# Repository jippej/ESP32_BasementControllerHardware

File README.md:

# JEEC Basement Controller Board
 A sensor and controller board based on WT32-ETH01

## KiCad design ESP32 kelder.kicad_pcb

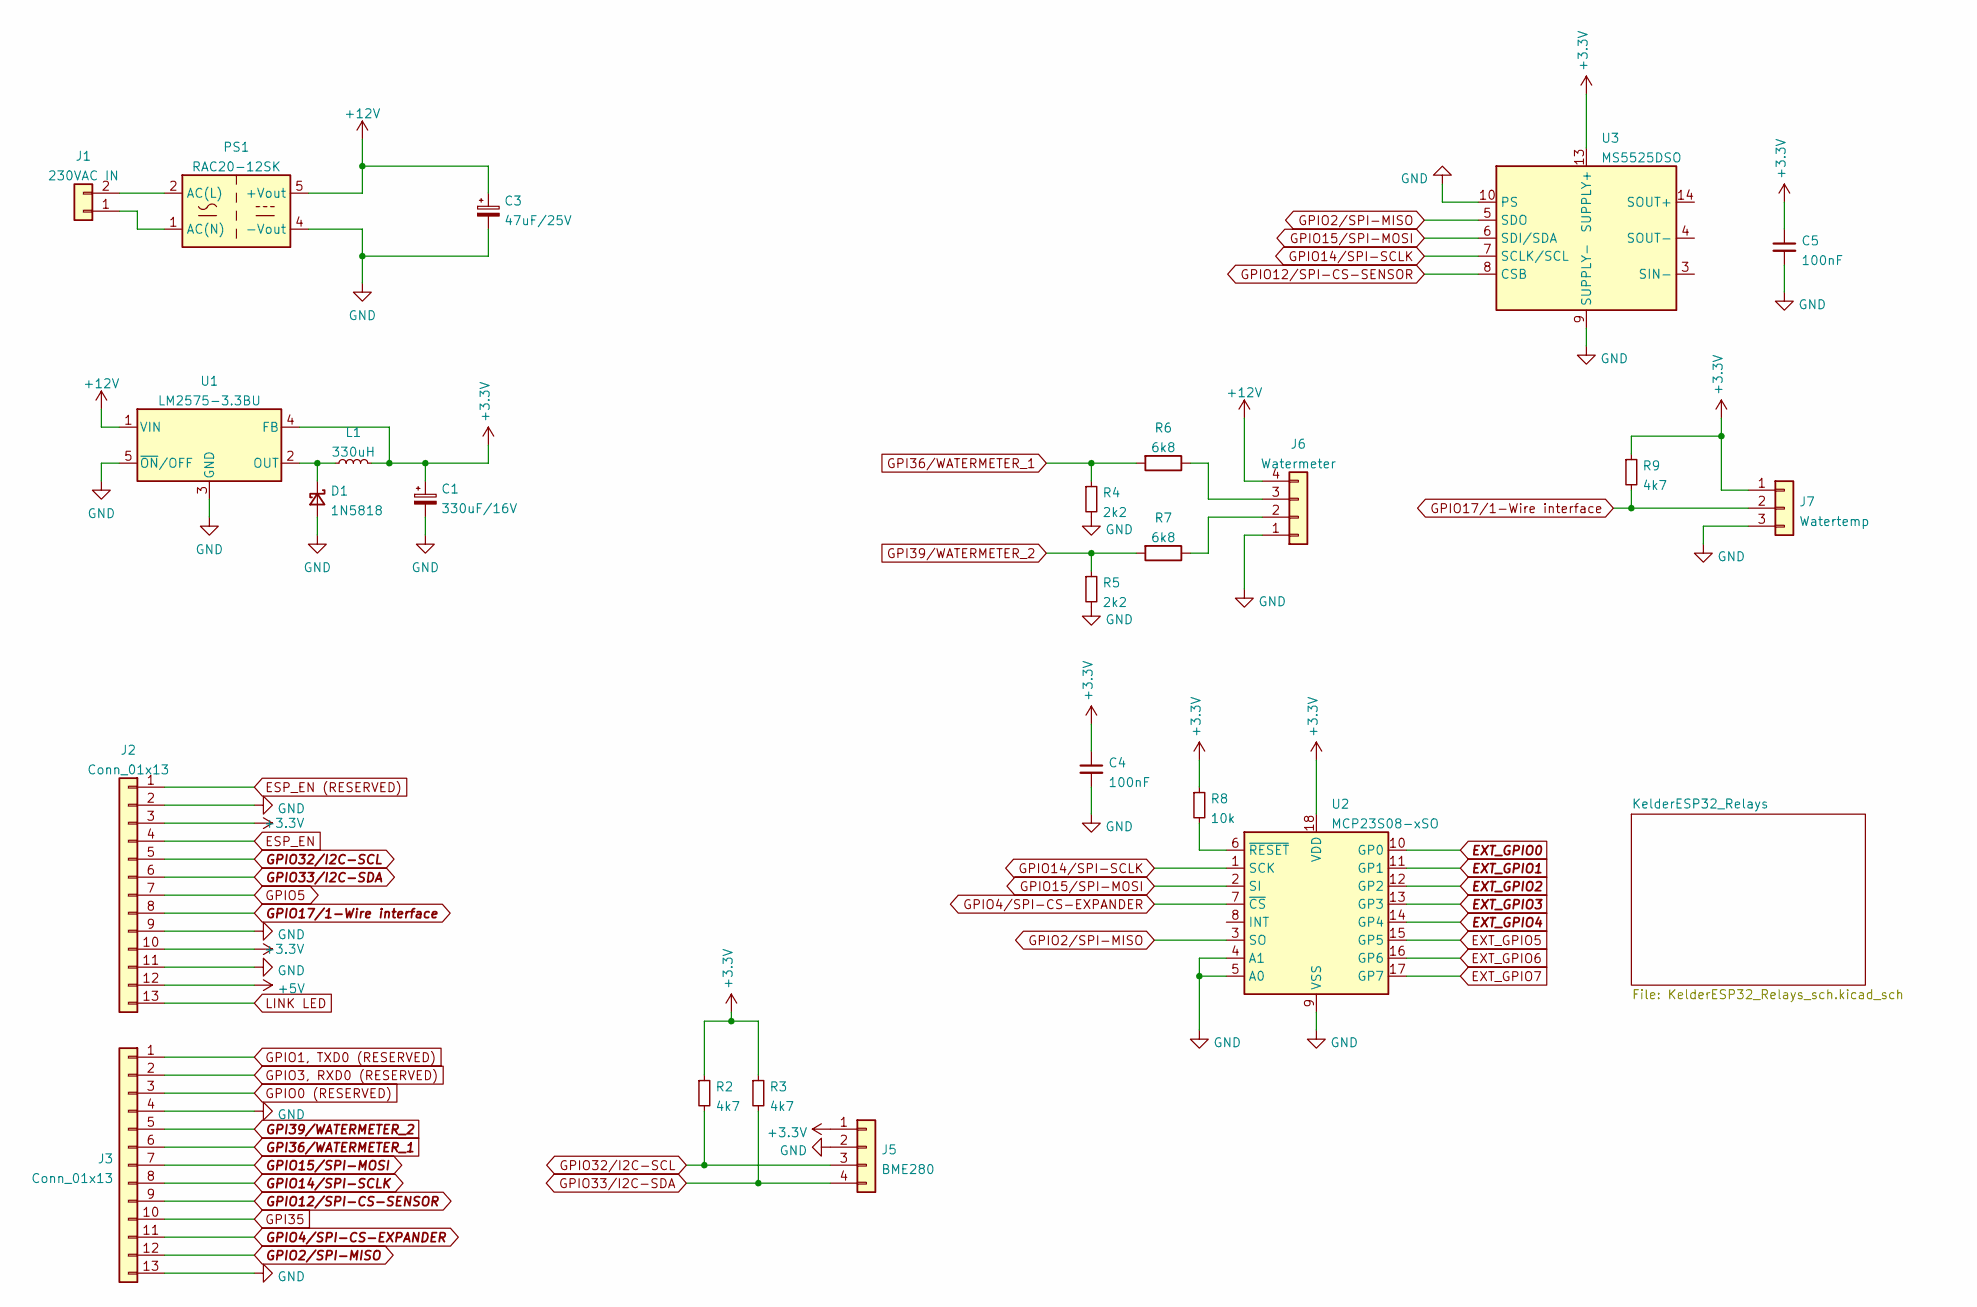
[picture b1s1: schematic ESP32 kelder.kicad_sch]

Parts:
C1: 330uF/16V; CP_Elec_8x10.5
C3: 47uF/25V; CP_Radial_D5.0mm_P2.00mm
C4, C5: 100nF; C_0805_2012Metric_Pad1.18x1.45mm_HandSolder
D1: 1N5818; D_DO-41_SOD81_P10.16mm_Horizontal
J1: 230VAC IN; TerminalBlock_Phoenix_MKDS-3-2-5.08_1x02_P5.08mm_Horizontal
J2, J3: Conn_01x13; PinSocket_1x13_P2.54mm_Vertical
J5: BME280; TerminalBlock_Phoenix_MKDS-1,5-4-5.08_1x04_P5.08mm_Horizont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
J6: Watermeter; TerminalBlock_Phoenix_MKDS-1,5-4-5.08_1x04_P5.08mm_Horizont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
J7: Watertemp; TerminalBlock_Phoenix_MKDS-1,5-3-5.08_1x03_P5.08mm_Horizont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
L1: 330uH; L_Bourns-SRN1060
PS1: RAC20-12SK; Converter_ACDC_Recom_RAC20-xxSK_THT
R2, R3, R9: 4k7; R_0805_2012Metric_Pad1.20x1.40mm_HandSolder
R4, R5: 2k2; R_0805_2012Metric_Pad1.20x1.40mm_HandSolder
R6, R7: 6k8; R_0805_2012Metric_Pad1.20x1.40mm_HandSolder
R8: 10k; R_0805_2012Metric_Pad1.20x1.40mm_HandSolder
U1: LM2575-3.3BU; TO-263-5_TabPin3
U2: MCP23S08-xSO; SOIC-18W_7.5x11.6mm_P1.27mm
U3: MS5525DSO; SOIC-14W_7.5x9mm_P1.27mm

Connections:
+3V3: C1.1, C4.1, C5.1, J2.3, J2.10, J5.1, J7.1, L1.2, R2.1, R3.1, R8.1, R9.1, U1.4 (FB), U2.18 (VDD), U3.11 (SUPPLY+), U3.13 (SUPPLY+)
+5V: J2.12
+12V: C3.1, J6.4, PS1.5 (+Vout), U1.1 (VIN); also elsewhere on the board
ESP_EN: J2.4
ESP_EN (RESERVED): J2.1
EXT_GPIO0: U2.10 (GP0); also elsewhere on the board
EXT_GPIO1: U2.11 (GP1); also elsewhere on the board
EXT_GPIO2: U2.12 (GP2); also elsewhere on the board
EXT_GPIO3: U2.13 (GP3); also elsewhere on the board
EXT_GPIO4: U2.14 (GP4); also elsewhere on the board
EXT_GPIO5: U2.15 (GP5)
EXT_GPIO6: U2.16 (GP6)
EXT_GPIO7: U2.17 (GP7)
GND: C1.2, C3.2, C4.2, C5.2, D1.2 (A), J2.2, J2.9, J2.11, J3.4, J3.13, J5.2, J6.1, J7.3, PS1.4 (-Vout), R4.2, R5.2, U1.3 (GND), U1.5 (~ON/OFF), U2.4 (A1), U2.5 (A0), U2.9 (VSS), U3.9 (SUPPLY-), U3.10 (PS); also elsewhere on the board
GPI35: J3.10
GPI36/WATERMETER_1: J3.6, R4.1, R6.2
GPI39/WATERMETER_2: J3.5, R5.1, R7.2
GPIO0 (RESERVED): J3.3
GPIO1, TXD0 (RESERVED): J3.1
GPIO2/SPI-MISO: J3.12, U2.3 (SO), U3.5 (SDO)
GPIO3, RXD0 (RESERVED): J3.2
GPIO4/SPI-CS-EXPANDER: J3.11, U2.7 (~CS)
GPIO5: J2.7
GPIO12/SPI-CS-SENSOR: J3.9, U3.8 (CSB)
GPIO14/SPI-SCLK: J3.8, U2.1 (SCK), U3.7 (SCLK/SCL)
GPIO15/SPI-MOSI: J3.7, U2.2 (SI), U3.6 (SDI/SDA)
GPIO17/1-Wire interface: J2.8, J7.2, R9.2
GPIO32/I2C-SCL: J2.5, J5.3, R2.2
GPIO33/I2C-SDA: J2.6, J5.4, R3.2
LINK LED: J2.13
unnamed: D1.1 (K), L1.1, U1.2 (OUT)
unnamed: J1.1, PS1.1 (AC(N))
unnamed: J1.2, PS1.2 (AC(L))
unnamed: J6.2, R7.1
unnamed: J6.3, R6.1
unnamed: R8.2, U2.6 (~RESET)
unnamed: U3.1 (SIN-), U3.3 (SIN-)
unnamed: U3.2 (SOUT-), U3.4 (SOUT-)
unnamed: U3.12 (SOUT+), U3.14 (SOUT+)

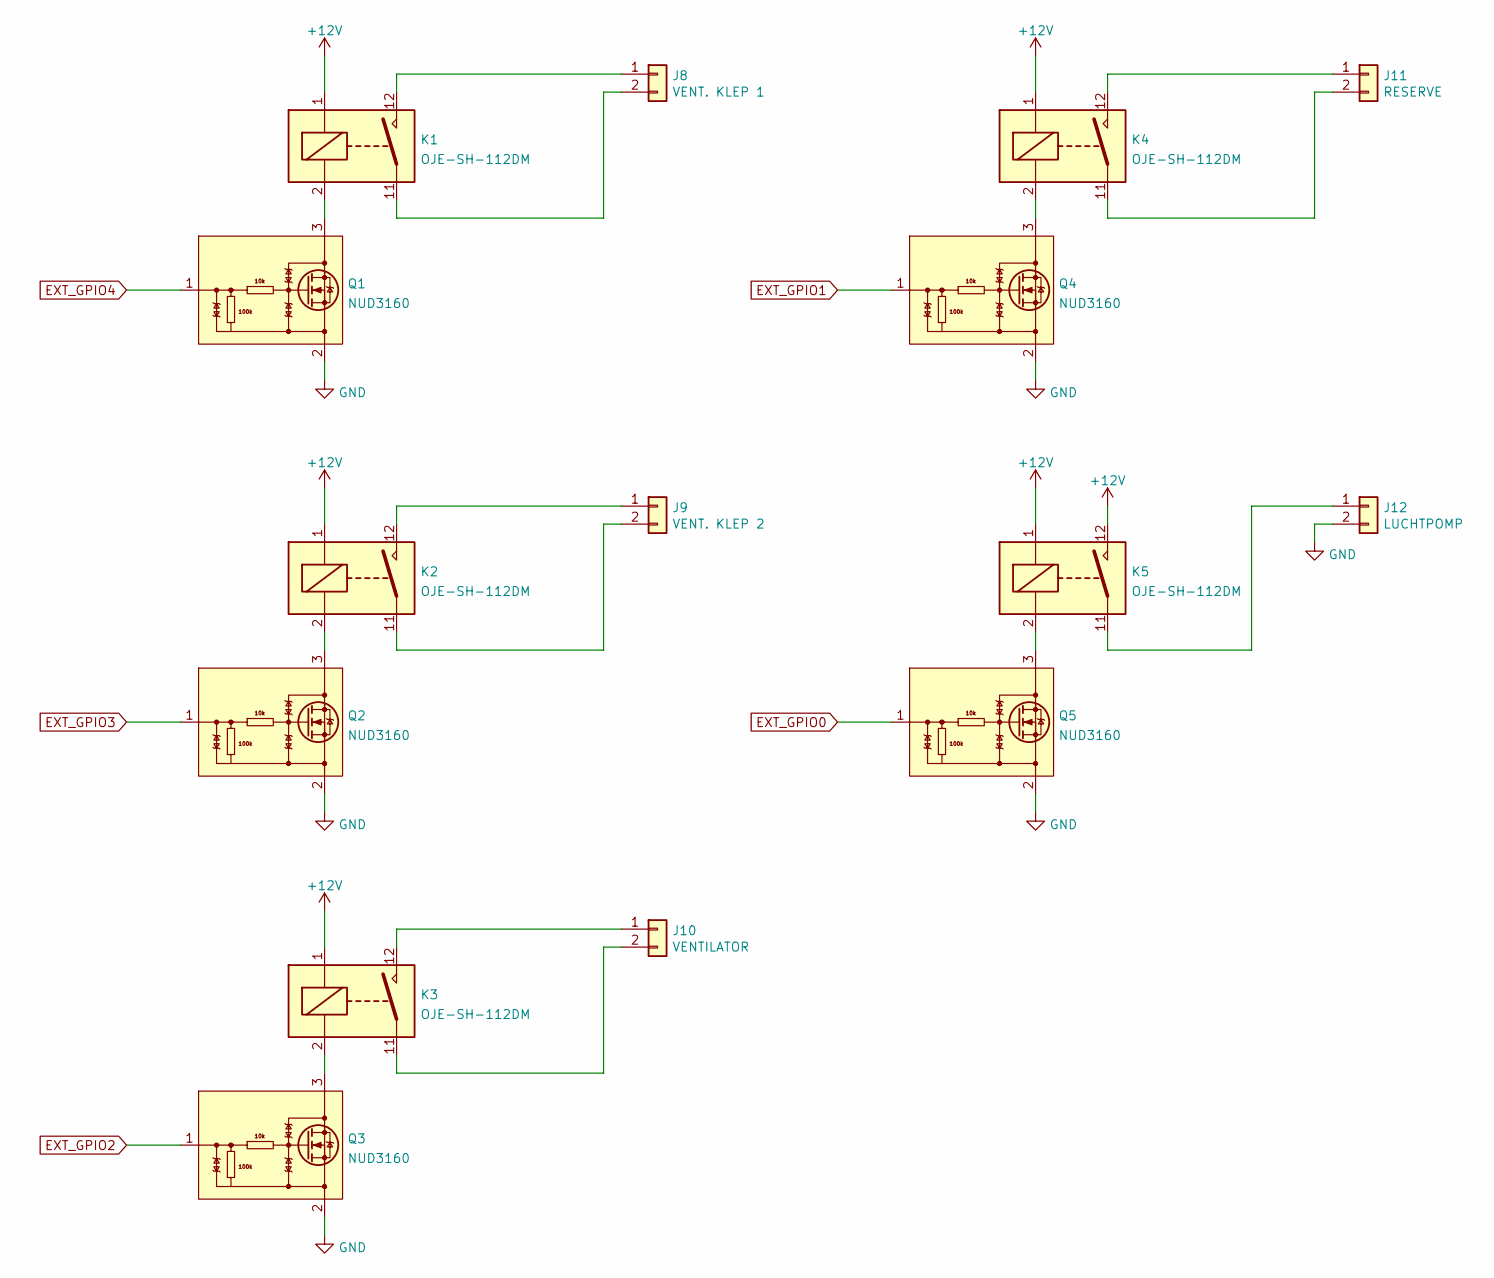
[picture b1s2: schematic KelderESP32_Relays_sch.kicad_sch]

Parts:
J8: VENT. KLEP 1; TerminalBlock_Phoenix_MKDS-3-2-5.08_1x02_P5.08mm_Horizontal
J9: VENT. KLEP 2; TerminalBlock_Phoenix_MKDS-3-2-5.08_1x02_P5.08mm_Horizontal
J10: VENTILATOR; TerminalBlock_Phoenix_MKDS-3-2-5.08_1x02_P5.08mm_Horizontal
J11: RESERVE; TerminalBlock_Phoenix_MKDS-3-2-5.08_1x02_P5.08mm_Horizontal
J12: LUCHTPOMP; TerminalBlock_Phoenix_MKDS-3-2-5.08_1x02_P5.08mm_Horizontal
K1, K2, K3, K4, K5: OJE-SH-112DM
Q1, Q2, Q3, Q4, Q5: NUD3160; SOT-23

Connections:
+12V: K1.1, K2.1, K3.1, K4.1, K5.1, K5.12; also elsewhere on the board
EXT_GPIO0: Q5.1 (G); also elsewhere on the board
EXT_GPIO1: Q4.1 (G); also elsewhere on the board
EXT_GPIO2: Q3.1 (G); also elsewhere on the board
EXT_GPIO3: Q2.1 (G); also elsewhere on the board
EXT_GPIO4: Q1.1 (G); also elsewhere on the board
GND: J12.2, Q1.2 (S), Q2.2 (S), Q3.2 (S), Q4.2 (S), Q5.2 (S); also elsewhere on the board
unnamed: J8.1, K1.12
unnamed: J8.2, K1.11
unnamed: J9.1, K2.12
unnamed: J9.2, K2.11
unnamed: J10.1, K3.12
unnamed: J10.2, K3.11
unnamed: J11.1, K4.12
unnamed: J11.2, K4.11
unnamed: J12.1, K5.11
unnamed: K1.2, Q1.3 (D)
unnamed: K2.2, Q2.3 (D)
unnamed: K3.2, Q3.3 (D)
unnamed: K4.2, Q4.3 (D)
unnamed: K5.2, Q5.3 (D)

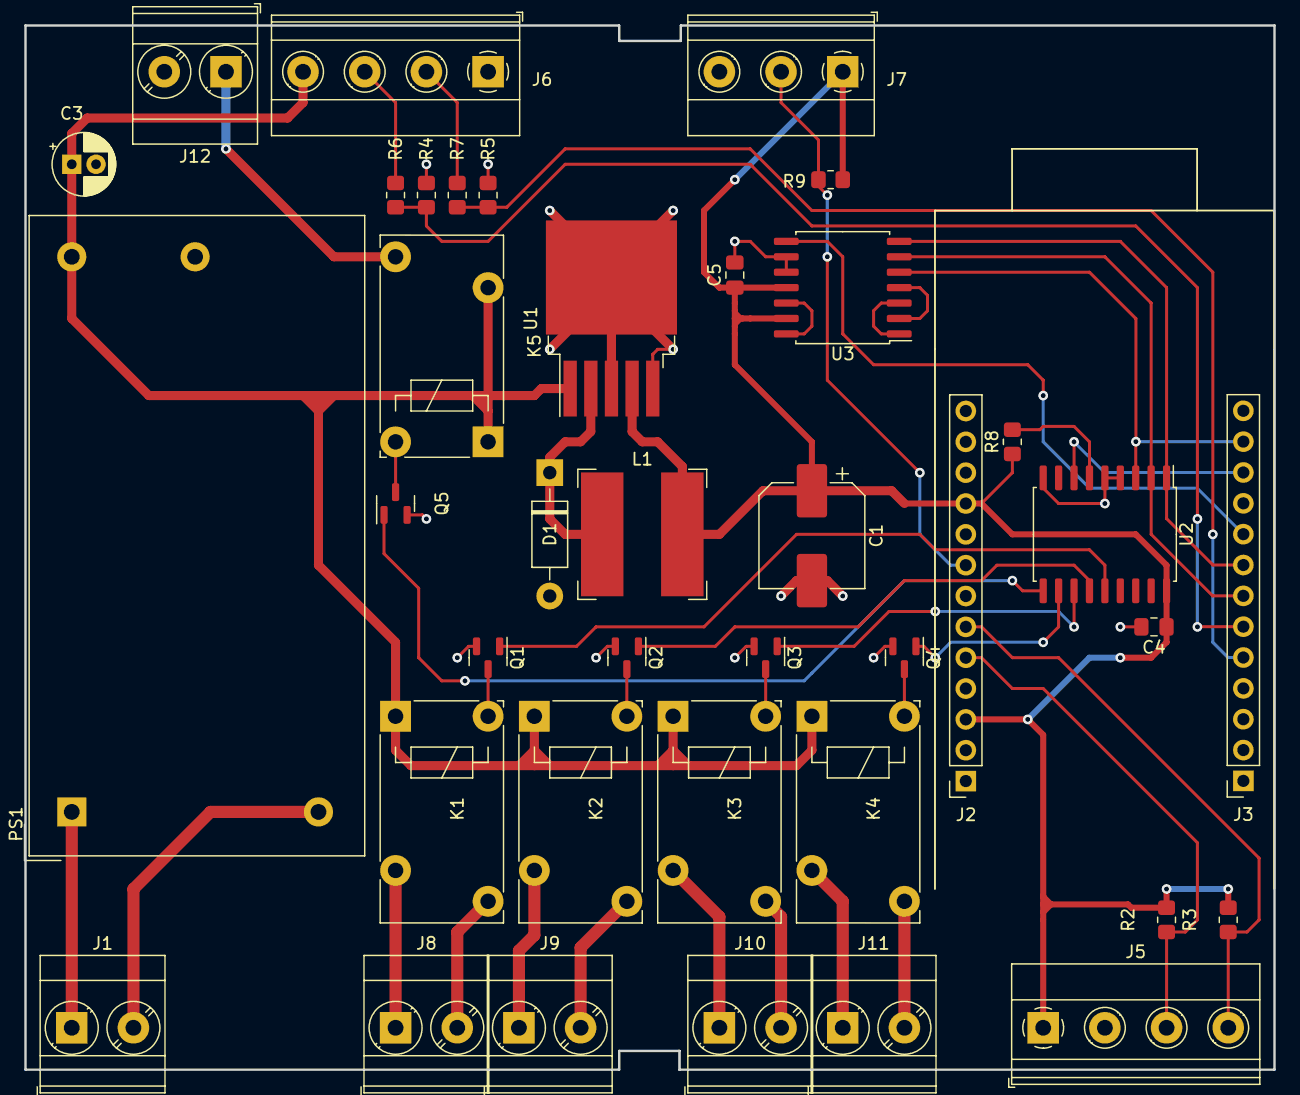
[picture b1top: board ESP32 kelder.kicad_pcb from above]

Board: 2 copper layers, 102.9 x 86.0 mm, 39 parts (0 on the bottom side), 41 nets.

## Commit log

2022-11-23 Initial commit rev0.1
    Initial commit rev 0.1

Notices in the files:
ESP32 kelder.kicad_pcb:
(c)2022 JEEC
